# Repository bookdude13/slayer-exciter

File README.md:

# slayer-exciter

EAGLE project for a Slayer Exciter circuit board.

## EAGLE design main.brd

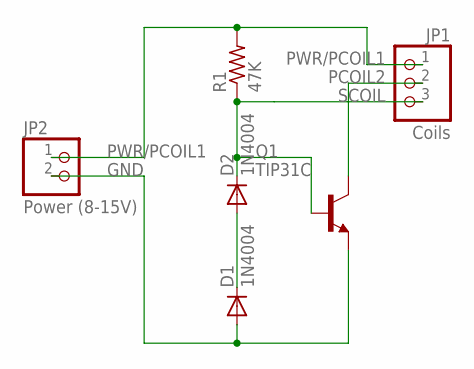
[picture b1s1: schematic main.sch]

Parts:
D1, D2: 1N4004; DO41-10
JP1: Coils; 1X03
JP2: Power (8-15V); 1X02
Q1: TIP31C; TO220
R1: 47K; R2512

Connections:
GND: D1.A, JP2.2, Q1.3 (E)
unnamed: D1.C, D2.A
PCOIL2: JP1.2, Q1.2 (C)
PWR/PCOIL1: JP1.1, JP2.1, R1.2
SCOIL: D2.C, JP1.3, Q1.1 (B), R1.1

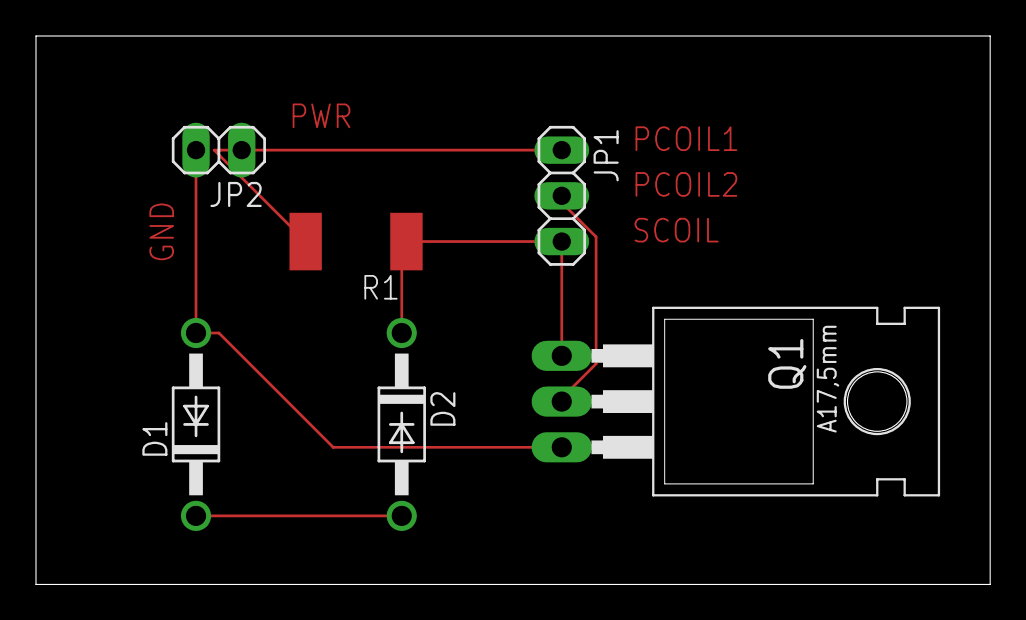
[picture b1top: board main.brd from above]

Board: 2 copper layers, 53.0 x 30.5 mm, 6 parts (0 on the bottom side), 5 nets.

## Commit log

2018-02-01 Initial commit, potentially working board and schematic
